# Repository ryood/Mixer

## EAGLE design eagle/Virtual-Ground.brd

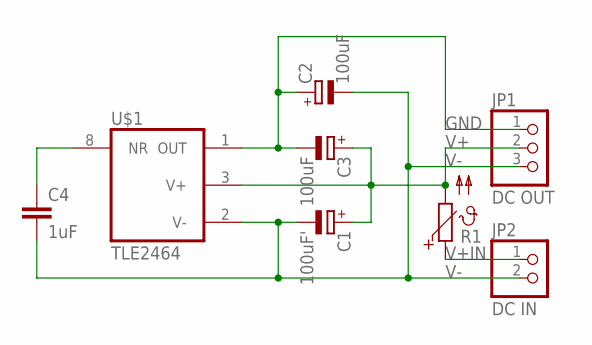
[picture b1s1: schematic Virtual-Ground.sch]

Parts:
C1: 100uF'; E2,5-6
C2, C3: 100uF; E2,5-6
C4: 1uF; C050-050X075
JP1: DC OUT; 1X03
JP2: DC IN; 1X02
R1: PTC660; P660
U$1: TLE2464

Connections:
GND: C2.+, C3.-, JP1.1, U$1.1 (OUT)
unnamed: C4.1, U$1.8 (NR)
V+: C1.+, C3.+, JP1.2, R1.2, U$1.3 (V+)
V+IN: JP2.1, R1.1
V-: C1.-, C2.-, C4.2, JP1.3, JP2.2, U$1.2 (V-)

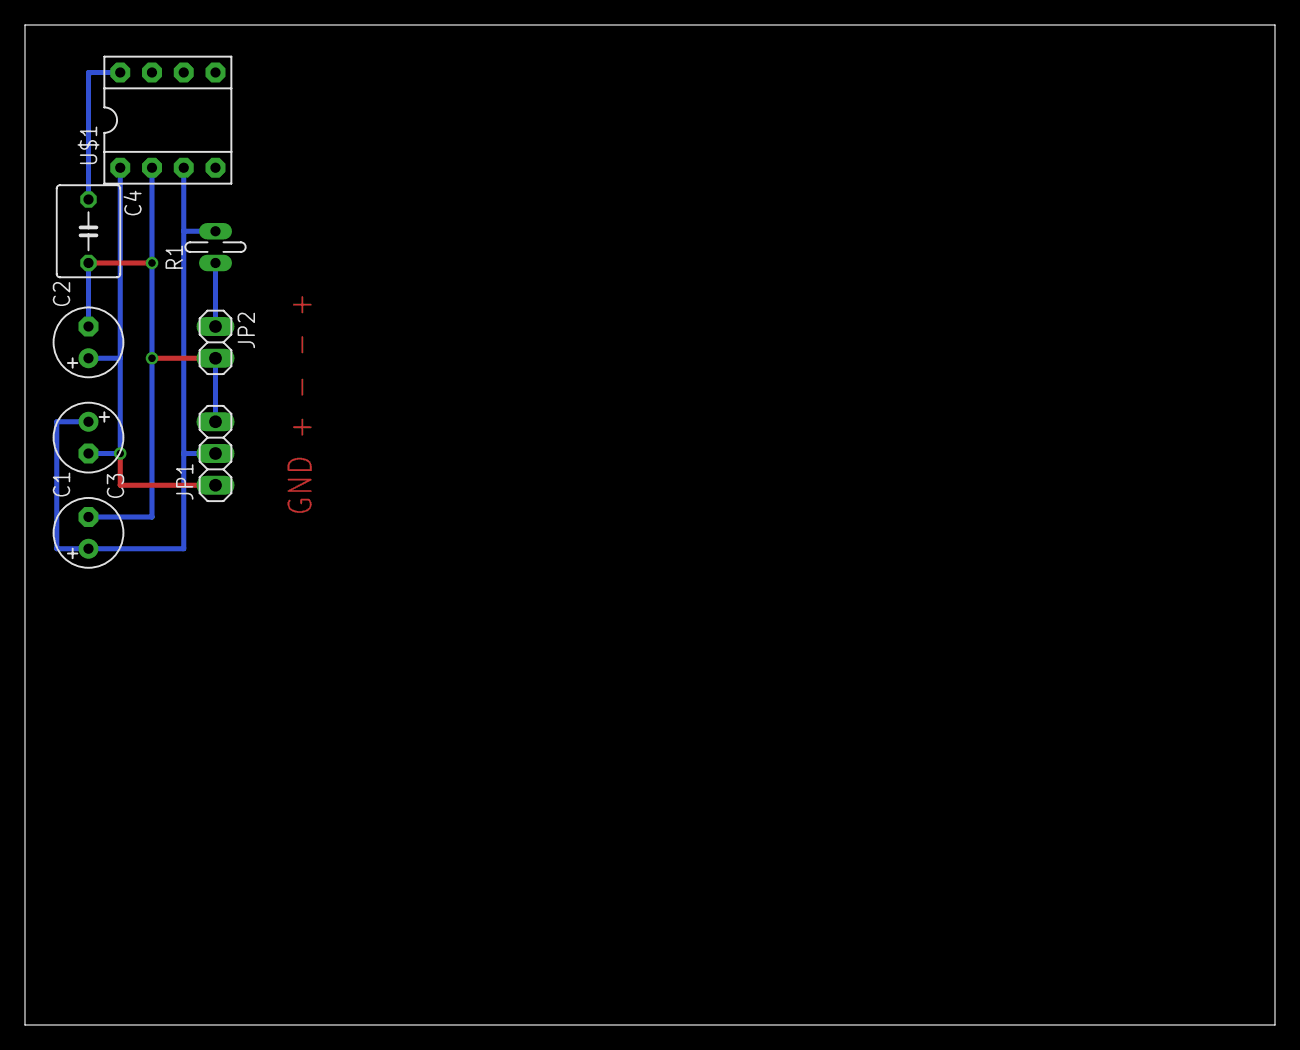
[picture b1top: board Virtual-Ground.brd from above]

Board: 2 copper layers, 100.0 x 80.0 mm, 8 parts (0 on the bottom side), 5 nets.

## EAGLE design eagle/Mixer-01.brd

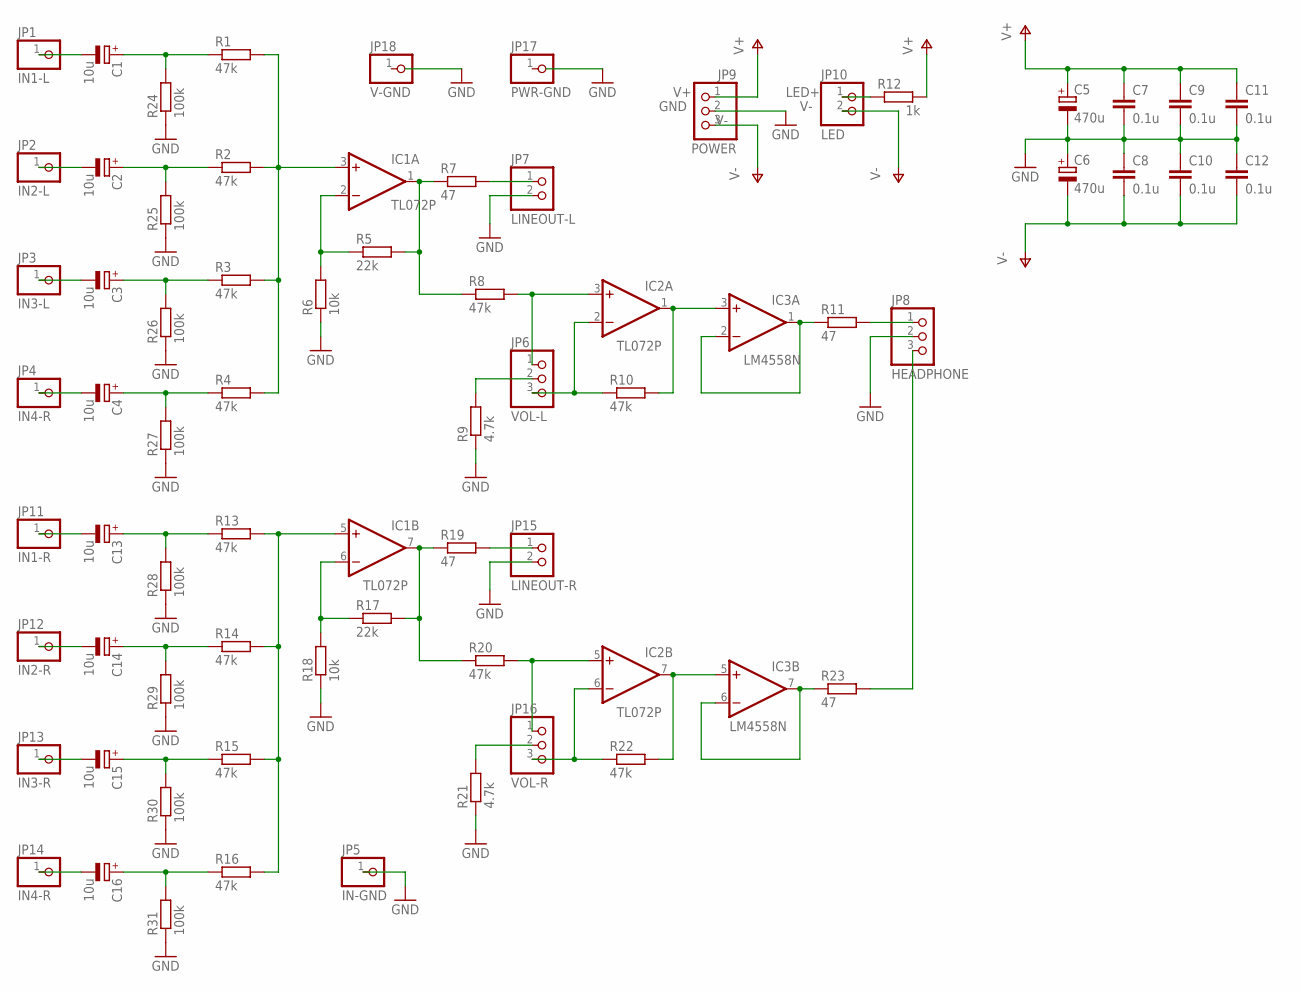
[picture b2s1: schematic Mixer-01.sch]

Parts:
C1, C2, C3, C4, C13, C14, C15, C16: 10u; E5-8,5
C5, C6: 470u; E7,5-16
C7, C8, C9, C10, C11, C12: 0.1u; C050-024X044
IC1, IC2: TL072P; DIL08
IC3: LM4558N; DIL08
JP1: IN1-L; 1X01
JP2: IN2-L; 1X01
JP3: IN3-L; 1X01
JP4, JP14: IN4-R; 1X01
JP5: IN-GND; 1X01
JP6: VOL-L; 1X03
JP7: LINEOUT-L; 1X02
JP8: HEADPHONE; 1X03
JP9: POWER; 1X03
JP10: LED; 1X02
JP11: IN1-R; 1X01
JP12: IN2-R; 1X01
JP13: IN3-R; 1X01
JP15: LINEOUT-R; 1X02
JP16: VOL-R; 1X03
JP17: PWR-GND; 1X01
JP18: V-GND; 1X01
R1, R2, R3, R4, R8, R10, R13, R14, R15, R16, R20, R22: 47k; 0207/7
R5, R17: 22k; 0207/7
R6, R18: 10k; 0207/7
R7, R11, R19, R23: 47; 0207/7
R9, R21: 4.7k; 0207/7
R12: 1k; 0207/7
R24, R25, R26, R27, R28, R29, R30, R31: 100k; 0207/7

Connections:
GND: C5.-, C6.+, C7.2, C8.1, C9.2, C10.1, C11.2, C12.1, JP5.1, JP7.2, JP8.2, JP9.2, JP15.2, R6.1, R9.1, R18.1, R21.1, R24.1, R25.1, R26.1, R27.1, R28.1, R29.1, R30.1, R31.1
LED+: JP10.1, R12.1
unnamed: C1.-, JP1.1
unnamed: C2.-, JP2.1
unnamed: C3.-, JP3.1
unnamed: C4.-, JP4.1
unnamed: JP6.2, R9.2
unnamed: C13.+, R13.1, R28.2
unnamed: C14.+, R14.1, R29.2
unnamed: C1.+, R1.1, R24.2
unnamed: C2.+, R2.1, R25.2
unnamed: C3.+, R3.1, R26.2
unnamed: C4.+, R4.1, R27.2
unnamed: IC1.3 (+IN), R1.2, R2.2, R3.2, R4.2
unnamed: IC1.2 (-IN), R5.1, R6.2
unnamed: IC1.1 (OUT), R5.2, R7.1, R8.1
unnamed: JP7.1, R7.2
unnamed: IC2.3 (+IN), JP6.1, R8.2
unnamed: C15.+, R15.1, R30.2
unnamed: IC2.2 (-IN), JP6.3, R10.1
unnamed: IC2.1 (OUT), IC3.3 (+IN), R10.2
unnamed: IC3.1 (OUT), IC3.2 (-IN), R11.1
unnamed: JP8.1, R11.2
unnamed: C16.+, R16.1, R31.2
unnamed: IC1.5 (+IN), R13.2, R14.2, R15.2, R16.2
unnamed: IC1.6 (-IN), R17.1, R18.2
unnamed: IC1.7 (OUT), R17.2, R19.1, R20.1
unnamed: JP15.1, R19.2
unnamed: IC2.5 (+IN), JP16.1, R20.2
unnamed: IC2.6 (-IN), JP16.3, R22.1
unnamed: IC2.7 (OUT), IC3.5 (+IN), R22.2
unnamed: IC3.6 (-IN), IC3.7 (OUT), R23.1
unnamed: JP8.3, R23.2
unnamed: C13.-, JP11.1
unnamed: C14.-, JP12.1
unnamed: C15.-, JP13.1
unnamed: C16.-, JP14.1
unnamed: JP16.2, R21.2
V+: C5.+, C7.1, C9.1, C11.1, IC1.8 (V+), IC2.8 (V+), IC3.8 (V+), JP9.1, R12.2
V-: C6.-, C8.2, C10.2, C12.2, IC1.4 (V-), IC2.4 (V-), IC3.4 (V-), JP9.3, JP10.2

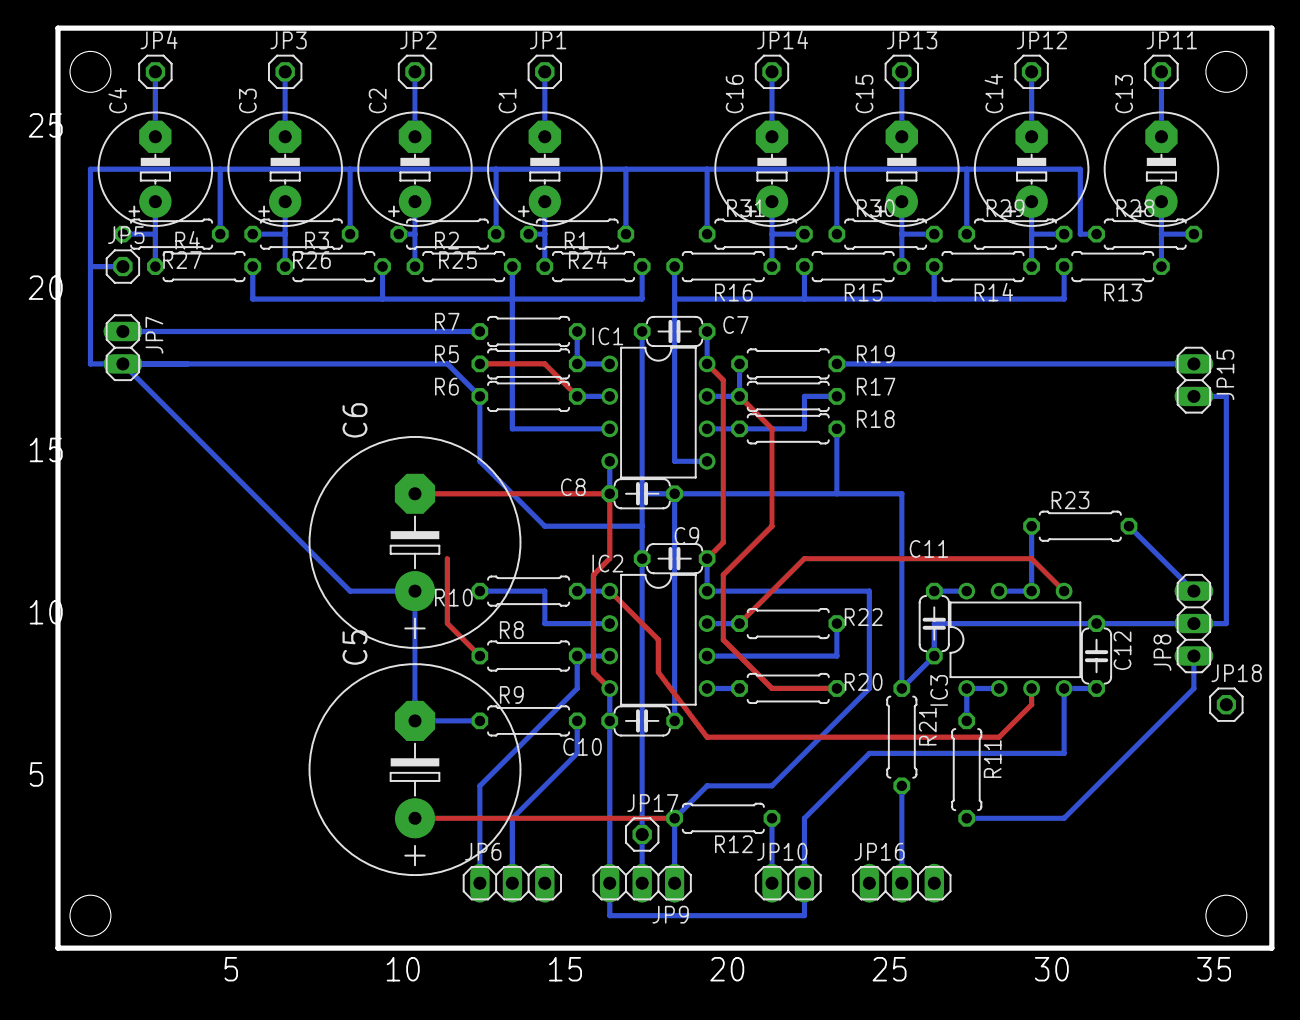
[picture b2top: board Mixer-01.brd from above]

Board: 2 copper layers, 97.3 x 75.4 mm, 68 parts (0 on the bottom side), 40 nets.

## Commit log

2014-07-01 Mixer-01.brd 結線を修正
2014-07-02 Mixer-01.brd: ICを水平に
2014-07-02 Mixer-01.brd: 修正
2014-07-02 Mixer結線図.ai: 修正 Mixer-01.brd: 修正
2014-07-02 Mixer-01.brd: グリッドを修正
2014-07-05 TestChart.xlsx: 追加
    その他修正
2014-07-10 電池ボックスのGNDの配線を変更
2014-07-10 テストを結果記入
2014-07-10 テスト結果追加
2014-07-10 Mixer結線図 - テスト用.ai: 追加
2014-07-15 通電状態テスト項目追加
2014-07-17 OPAMPの入力を接地
2014-07-17 Mixer-01.brd: 配線を修正
2014-07-20 結線図修正： GND線追加
2014-07-20 Mixer-Case.dwg: ケース加工図追加
2014-07-22 ケース加工図修正
2014-08-02 ケース加工図 Hole Size 修正
2014-08-05 Mixer結線図修正 RCAジャックーPOTのGND線削除
2014-09-14 仮想グランド基板の設計図を追加
2014-09-14 基板設計図修正
2014-09-14 ケース加工図修正： 仮想グランド基板、DCジャック、電源切り替えスイッチ追加
2014-09-14 Mixer結線図にV-GNDを追加 V-GND基板設計図を修正
2014-09-14 Mixer基板設計図にV-GND用ピンを追加
2014-09-16 Mixer結線図修正
2014-09-16 仮想グランド基板設計図修正
